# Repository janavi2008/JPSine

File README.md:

# JPSine
a scientific calculator running on a raspberry pi pico, with a 2.42in oled screen, 40 buttons, using a 1000mAh 3.7V lipo battery. im trying to get it as close to a real scientific calculator that can be used regularly, so the firmware will keep changing once the initial build is done, ill be adding more functions, making it easier/more intuitive to use. the current firmware is the best i could do without testing.

# Design
the buttons are arranged in a matrix with 8 rows and 5 columns, with a diode for each button, so even if 2 buttons are pressed together theres no issue as it only lets current pass in one direction. one leg of all the leds in one row is passed through a diode and then connected together to a GPIO pin on the pico, and one leg of all leds in one column is tied together to another GPIO. this way, only 13 pins are needed to read 40 buttons - one for each row and column.

im using TP4056 module for charging the battery, and it also provides protection from over charging, over current, etc. the OLED Screen uses I2C, so it only needs 2 pins on the pico - SDA and SCL. it also has a slide switch for power, and a push button for reset.

when a button press is detected, the firmware first has to scan which button it was, and then which funtion it maps to, by checking it against an array of the keys (there are separate arrays if shif or alpha are on, so it has to check for that too). if its number, operator, or function, it has to be added to the end of an expression that builds up until the equal to button is pressed. once the equals button is pressed, it has to calculate the result. first it groups the digits and classifies each part of the expression as a number, operator, funtion or bracket. it has to add a multiplication for expressions like 3(7-1) or 4sin30. next it has to rewrite the expression in reverse parish notation(rpn) - e.g 4+7*5 becomes 4 7 5 * +. now it can evaluate this rpn expression and display the result, though it also has to check for syntax errors or things like dividing by 0.

# BOM

| Item | Quantity | Total Cost | Source |
| :--- | :---: | :---: | :--- |
| Raspberry Pi Pico | 1 | $4.50 | Robu |
| 3.7V 1000mAh battery | 1 | $1.60 | Hubtronics |
| TP4056 module | 1 | $0.15 | Robu |
| 2.42in OLED screen | 1 | $15.00 | Zbotic |
| 10uF 0603 capacitor | 2 | $0.10 | Robu |
| 0.1uF 0603 capacitor | 2 | $0.10 | Robu |
| 100k 0603 resistor | 2 | $0.10 | Robu |
| 4.7k 0603 resistor | 2 | $0.10 | Robu |
| PTS 647 push buttons | 40 | $5.50 | Robu |
| SS14 Schottky diode | 1 | $0.10 | Robu |
| SOD-523 diode | 40 | $0.20 | Robu |
| PCM12SMTR slide switch | 1 | $0.60 | Robu |
| PCB | 1 | $4.00 | JLCPCB |

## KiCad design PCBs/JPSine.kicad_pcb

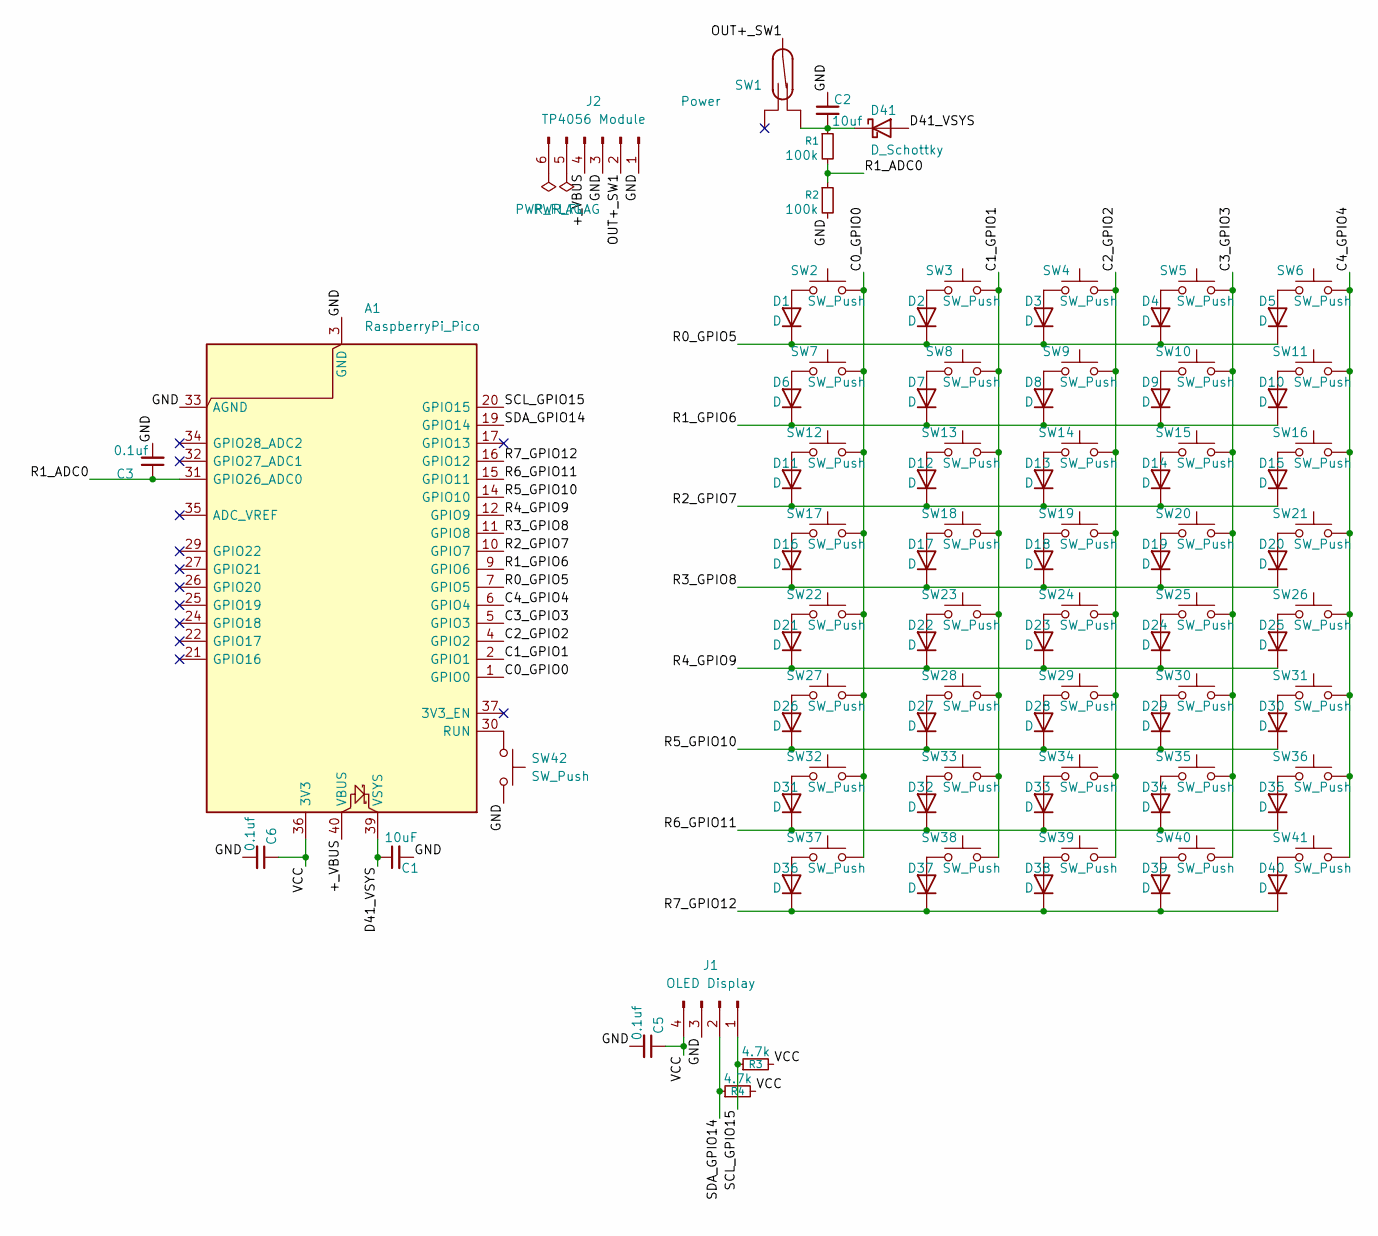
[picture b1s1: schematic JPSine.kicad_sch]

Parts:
A1: RaspberryPi_Pico; RaspberryPi_Pico_Common_SMD
C1: 10uF; C_0603_1608Metric_Pad1.08x0.95mm_HandSolder
C2: 10uf; C_0603_1608Metric_Pad1.08x0.95mm_HandSolder
C3, C5, C6: 0.1uf; C_0603_1608Metric_Pad1.08x0.95mm_HandSolder
D1, D2, D3, D4, D5, D6, D7, D8, D9, D10, D11, D12, D13, D14, D15, D16, D17, D18, D19, D20, D21, D22, D23, D24, D25, D26, D27, D28, D29, D30, D31, D32, D33, D34, D35, D36, D37, D38, D39, D40: D; D_0603_1608Metric_Pad1.05x0.95mm_HandSolder
D41: D_Schottky; D_SMA_Handsoldering
J1: OLED Display; PinHeader_1x04_P2.54mm_Vertical
J2: TP4056 Module; PinHeader_1x06_P2.54mm_Vertical
R1, R2: 100k; R_0603_1608Metric_Pad0.98x0.95mm_HandSolder
R3, R4: 4.7k; R_0603_1608Metric_Pad0.98x0.95mm_HandSolder
SW1: Power; SW_SPDT_PCM12
SW2, SW3, SW4, SW5, SW6, SW7, SW8, SW9, SW10, SW11, SW12, SW13, SW14, SW15, SW16, SW17, SW18, SW19, SW20, SW21, SW22, SW23, SW24, SW25, SW26, SW27, SW28, SW29, SW30, SW31, SW32, SW33, SW34, SW35, SW36, SW37, SW38, SW39, SW40, SW41, SW42: SW_Push; SW_SPST_PTS647_Sx38

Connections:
/+_VBUS: A1.40 (VBUS), J2.4
/C0_GPIO0: A1.1 (GPIO0), SW2.2, SW7.2, SW12.2, SW17.2, SW22.2, SW27.2, SW32.2, SW37.2
/C1_GPIO1: A1.2 (GPIO1), SW3.2, SW8.2, SW13.2, SW18.2, SW23.2, SW28.2, SW33.2, SW38.2
/C2_GPIO2: A1.4 (GPIO2), SW4.2, SW9.2, SW14.2, SW19.2, SW24.2, SW29.2, SW34.2, SW39.2
/C3_GPIO3: A1.5 (GPIO3), SW5.2, SW10.2, SW15.2, SW20.2, SW25.2, SW30.2, SW35.2, SW40.2
/C4_GPIO4: A1.6 (GPIO4), SW6.2, SW11.2, SW16.2, SW21.2, SW26.2, SW31.2, SW36.2, SW41.2
/D41_VSYS: A1.39 (VSYS), C1.1, D41.2 (A)
/GND: A1.3 (GND), A1.8 (GND), A1.13 (GND), A1.18 (GND), A1.23 (GND), A1.28 (GND), A1.33 (AGND), A1.38 (GND), C1.2, C2.1, C3.2, C5.2, C6.2, J1.3, J2.1, J2.3, R2.2, SW42.2
/OUT+_SW1: J2.2, SW1.2
/R0_GPIO5: A1.7 (GPIO5), D1.1 (K), D2.1 (K), D3.1 (K), D4.1 (K), D5.1 (K)
/R1_ADC0: A1.31 (GPIO26_ADC0), C3.1, R1.2, R2.1
/R1_GPIO6: A1.9 (GPIO6), D6.1 (K), D7.1 (K), D8.1 (K), D9.1 (K), D10.1 (K)
/R2_GPIO7: A1.10 (GPIO7), D11.1 (K), D12.1 (K), D13.1 (K), D14.1 (K), D15.1 (K)
/R3_GPIO8: A1.11 (GPIO8), D16.1 (K), D17.1 (K), D18.1 (K), D19.1 (K), D20.1 (K)
/R4_GPIO9: A1.12 (GPIO9), D21.1 (K), D22.1 (K), D23.1 (K), D24.1 (K), D25.1 (K)
/R5_GPIO10: A1.14 (GPIO10), D26.1 (K), D27.1 (K), D28.1 (K), D29.1 (K), D30.1 (K)
/R6_GPIO11: A1.15 (GPIO11), D31.1 (K), D32.1 (K), D33.1 (K), D34.1 (K), D35.1 (K)
/R7_GPIO12: A1.16 (GPIO12), D36.1 (K), D37.1 (K), D38.1 (K), D39.1 (K), D40.1 (K)
/SCL_GPIO15: A1.20 (GPIO15), J1.1, R3.1
/SDA_GPIO14: A1.19 (GPIO14), J1.2, R4.1
/VCC: A1.36 (3V3), C5.1, C6.1, J1.4, R3.2, R4.2
unnamed: A1.30 (RUN), SW42.1
unnamed: D1.2 (A), SW2.1
unnamed: D2.2 (A), SW3.1
unnamed: D3.2 (A), SW4.1
unnamed: D4.2 (A), SW5.1
unnamed: D5.2 (A), SW6.1
unnamed: D6.2 (A), SW7.1
unnamed: D7.2 (A), SW8.1
unnamed: D8.2 (A), SW9.1
unnamed: D9.2 (A), SW10.1
unnamed: D10.2 (A), SW11.1
unnamed: D11.2 (A), SW12.1
unnamed: D12.2 (A), SW13.1
unnamed: D13.2 (A), SW14.1
unnamed: D14.2 (A), SW15.1
unnamed: D15.2 (A), SW16.1
unnamed: D16.2 (A), SW17.1
unnamed: D17.2 (A), SW18.1
unnamed: D18.2 (A), SW19.1
unnamed: D19.2 (A), SW20.1
unnamed: D20.2 (A), SW21.1
unnamed: D21.2 (A), SW22.1
unnamed: D22.2 (A), SW23.1
unnamed: D23.2 (A), SW24.1
unnamed: D24.2 (A), SW25.1
unnamed: D25.2 (A), SW26.1
unnamed: D26.2 (A), SW27.1
unnamed: D27.2 (A), SW28.1
unnamed: D28.2 (A), SW29.1
unnamed: D29.2 (A), SW30.1
unnamed: D30.2 (A), SW31.1
unnamed: D31.2 (A), SW32.1
unnamed: D32.2 (A), SW33.1
unnamed: D33.2 (A), SW34.1
unnamed: D34.2 (A), SW35.1
unnamed: D35.2 (A), SW36.1
unnamed: D36.2 (A), SW37.1
unnamed: D37.2 (A), SW38.1
unnamed: D38.2 (A), SW39.1
unnamed: D39.2 (A), SW40.1
unnamed: D40.2 (A), SW41.1
unnamed: C2.2, D41.1 (K), R1.1, SW1.1

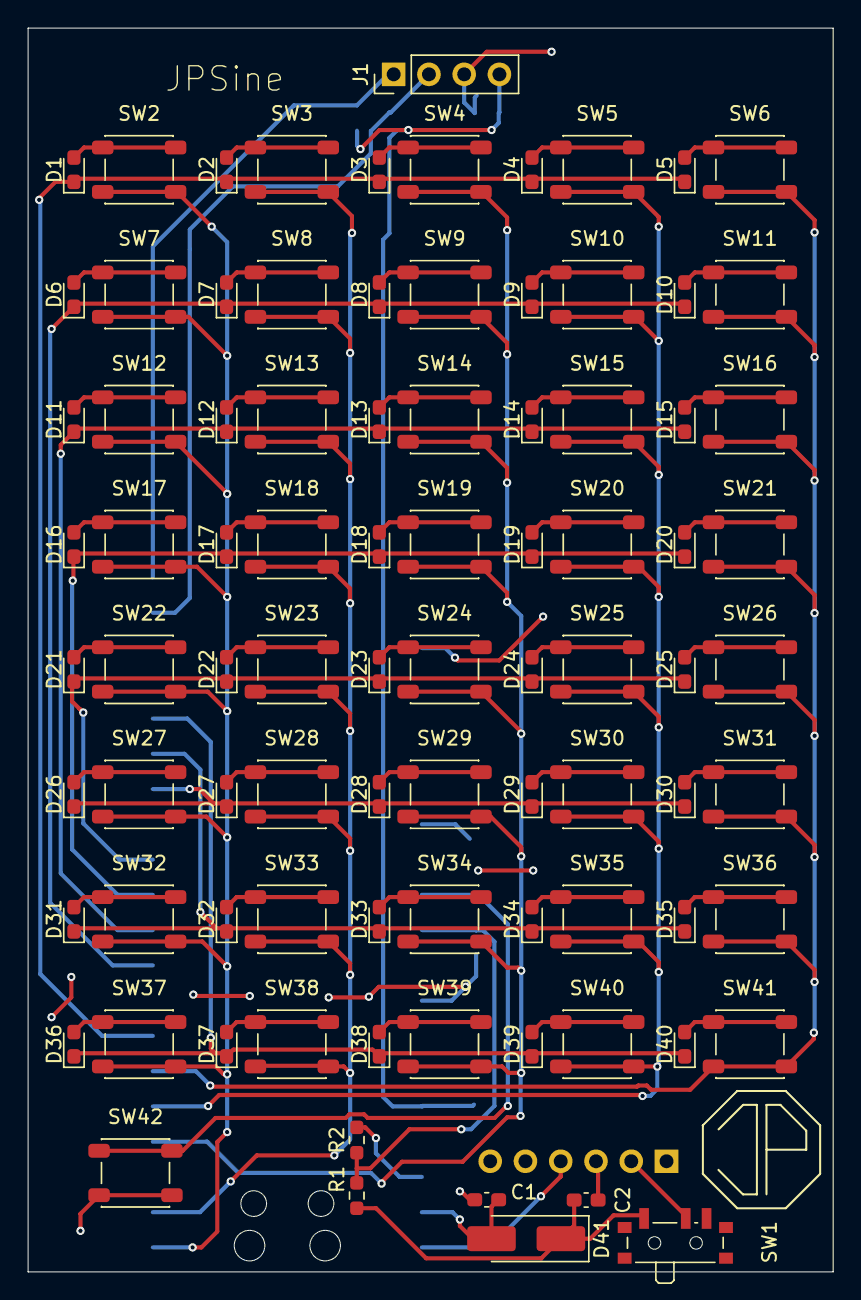
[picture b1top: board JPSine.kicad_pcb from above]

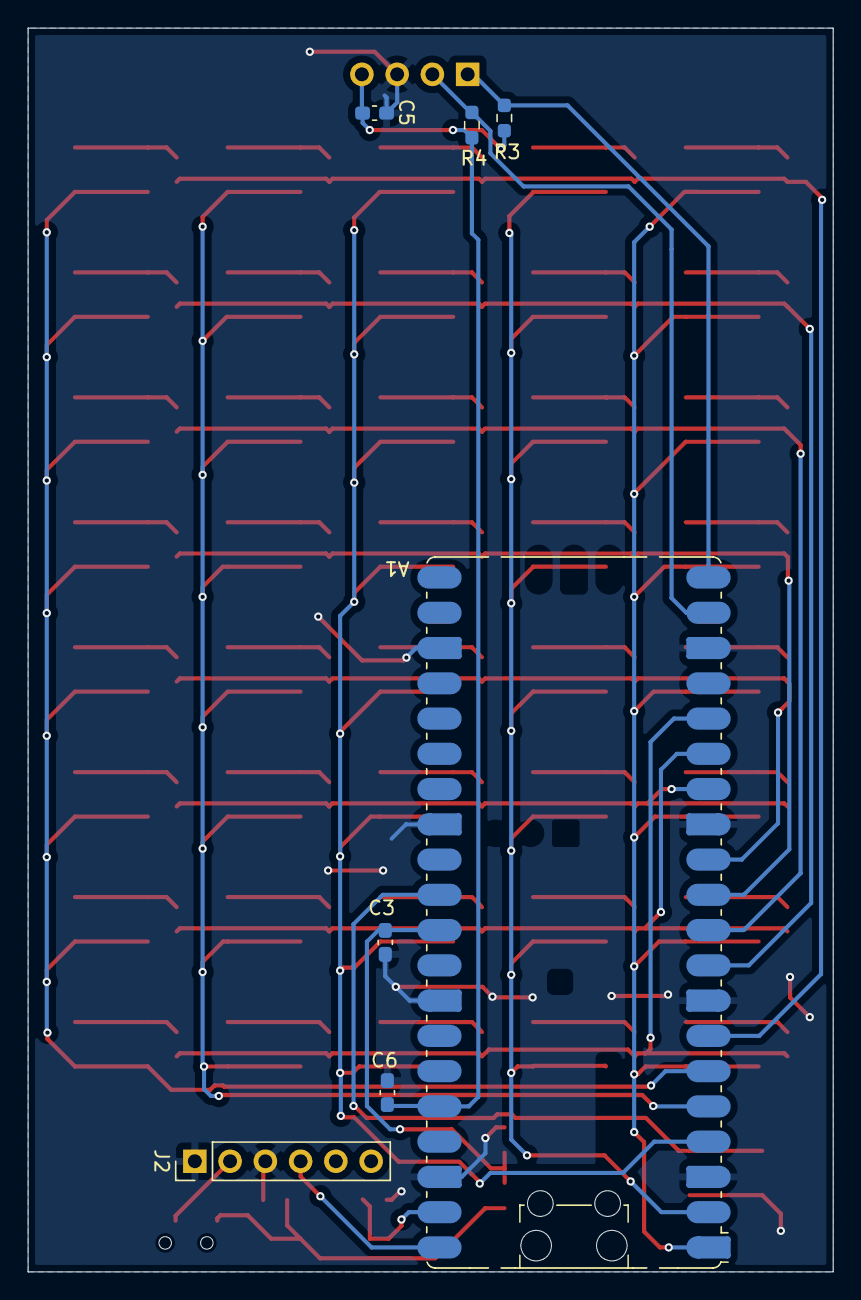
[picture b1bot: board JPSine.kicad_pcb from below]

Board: 2 copper layers, 58.0 x 89.6 mm, 95 parts (7 on the bottom side), 63 nets.
